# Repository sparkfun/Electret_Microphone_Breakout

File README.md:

Electret Microphone Breakout
============================

[*SparkFun Electret Microphone (BOB-09964)*](https://www.sparkfun.com/products/9964)

This small breakout board couples a small electret microphone 
with a 100x opamp to amplify the sounds of voice, door knocks, 
etc loud enough to be picked up by a microcontroller’s Analog to Digital converter. 

Repository Contents
-------------------
* **/Hardware** - All Eagle design files (.brd, .sch)

License Information
-------------------
The hardware is released under [Creative Commons ShareAlike 4.0 International](https://creativecommons.org/licenses/by-sa/4.0/).
The code is beerware; if you see me (or any other SparkFun employee) at the local, and you've found our code helpful, please buy us a round!

Distributed as-is; no warranty is given.

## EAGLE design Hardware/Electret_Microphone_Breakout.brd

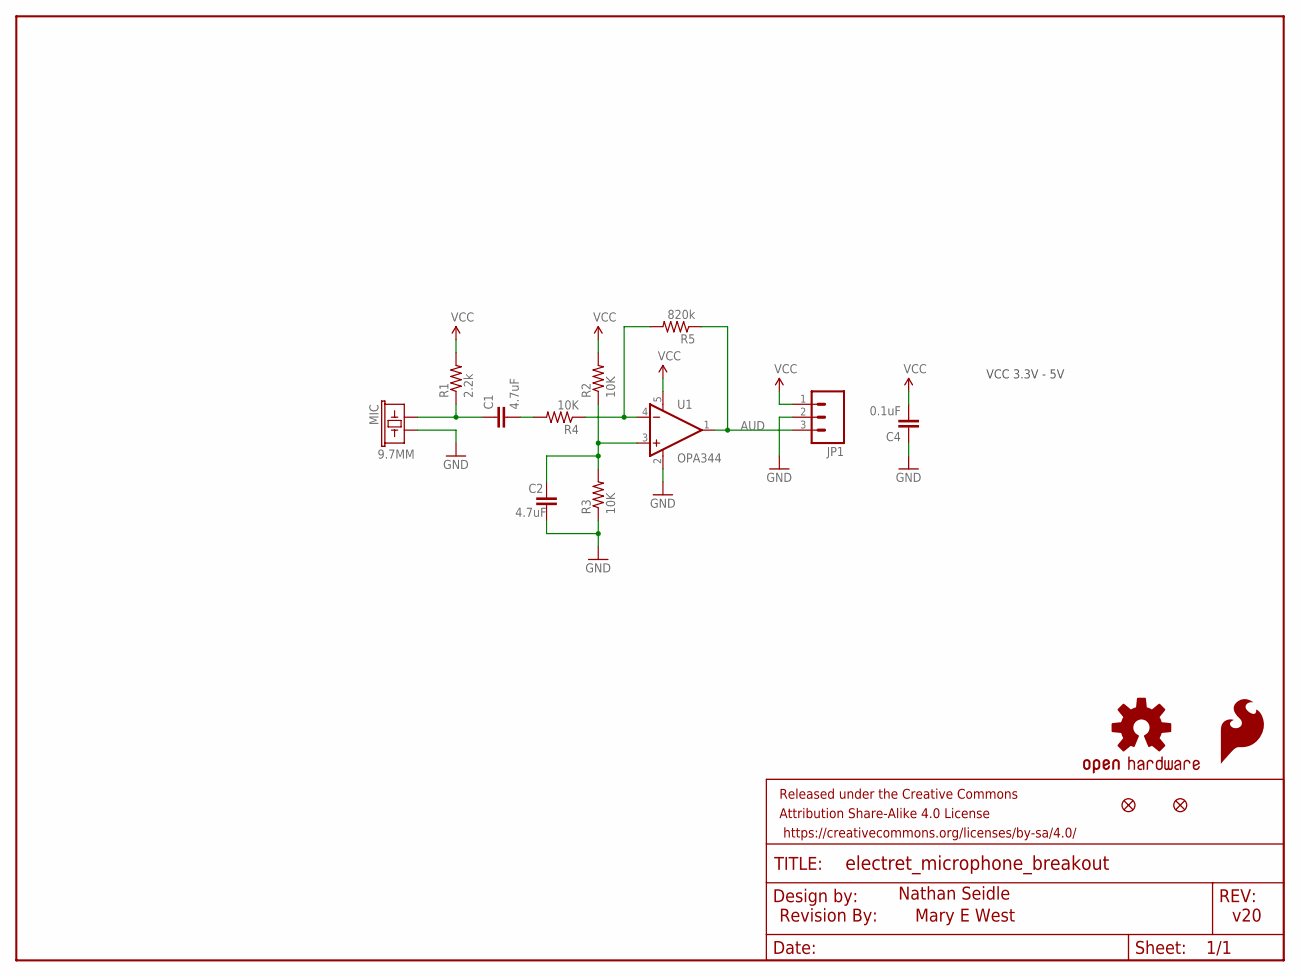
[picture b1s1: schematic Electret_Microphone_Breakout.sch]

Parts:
C1, C2: 4.7uF; 0603-CAP
C4: 0.1uF; 0603-CAP
FRAME1: FRAME-LETTER; CREATIVE_COMMONS
JP1: M03PTH; 1X03
JP2, JP3: FIDUCIALUFIDUCIAL; MICRO-FIDUCIAL
LOGO1: OSHW-LOGOMINI; OSHW-LOGO-MINI
MIC: 9.7MM; MIC-9.7MM
R1: 2.2k; 0603-RES
R2, R3, R4: 10K; 0603-RES
R5: 820k; 0603-RES
U1: OPA344; SOT23-5
U$1: SFE_LOGO_FLAME.1_INCH; SFE_LOGO_FLAME_.1
U$2: REVISION

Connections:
AUD: JP1.3, R5.1, U1.1 (OUT)
GND: C2.2, C4.1, JP1.2, MIC.2, R3.1, U1.2 (V-)
unnamed: C1.1, MIC.1, R1.1
unnamed: R4.1, R5.2, U1.4 (-IN)
unnamed: C1.2, R4.2
unnamed: C2.1, R2.1, R3.2, U1.3 (+IN)
VCC: C4.2, JP1.1, R1.2, R2.2, U1.5 (V+)

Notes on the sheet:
VCC 3.3V - 5V
v20
Mary E West
Nathan Seidle

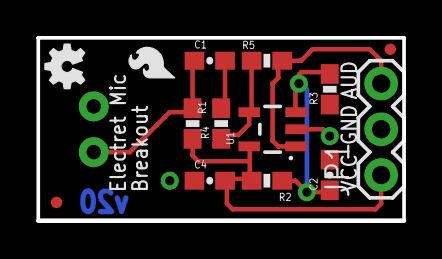
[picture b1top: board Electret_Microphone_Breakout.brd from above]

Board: 2 copper layers, 20.3 x 10.2 mm, 17 parts (1 on the bottom side), 7 nets.

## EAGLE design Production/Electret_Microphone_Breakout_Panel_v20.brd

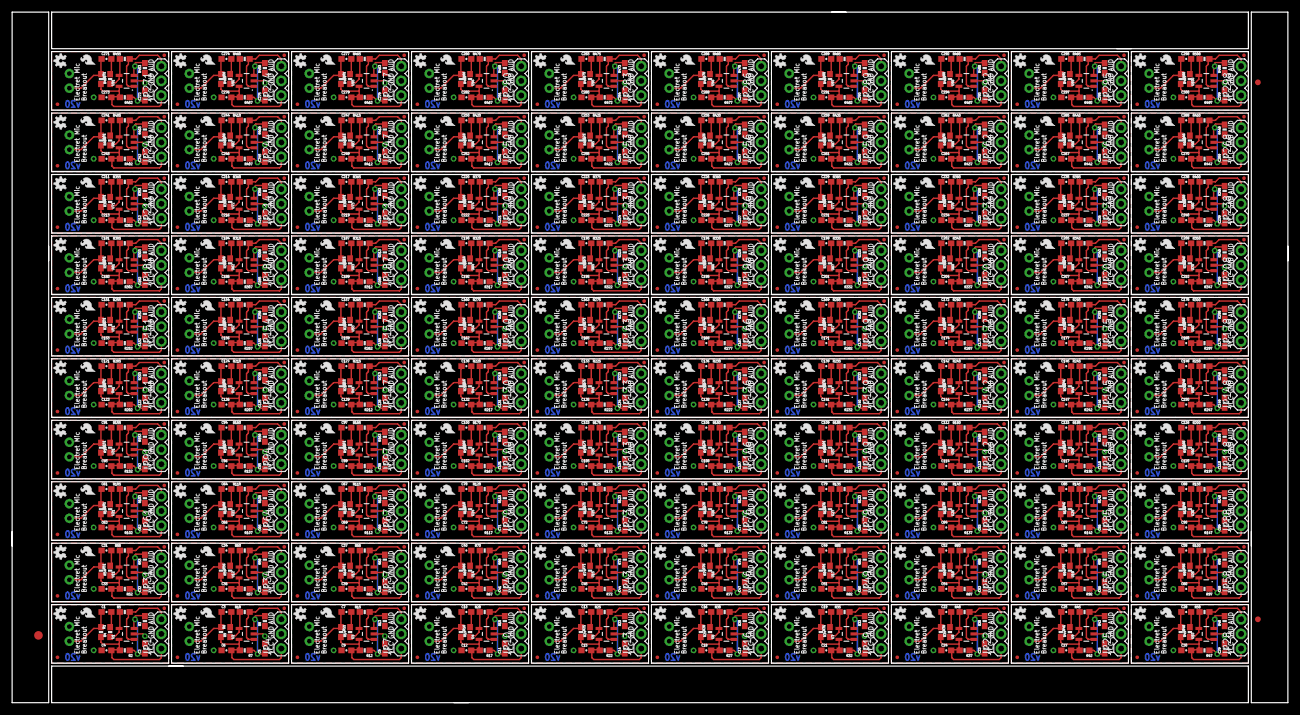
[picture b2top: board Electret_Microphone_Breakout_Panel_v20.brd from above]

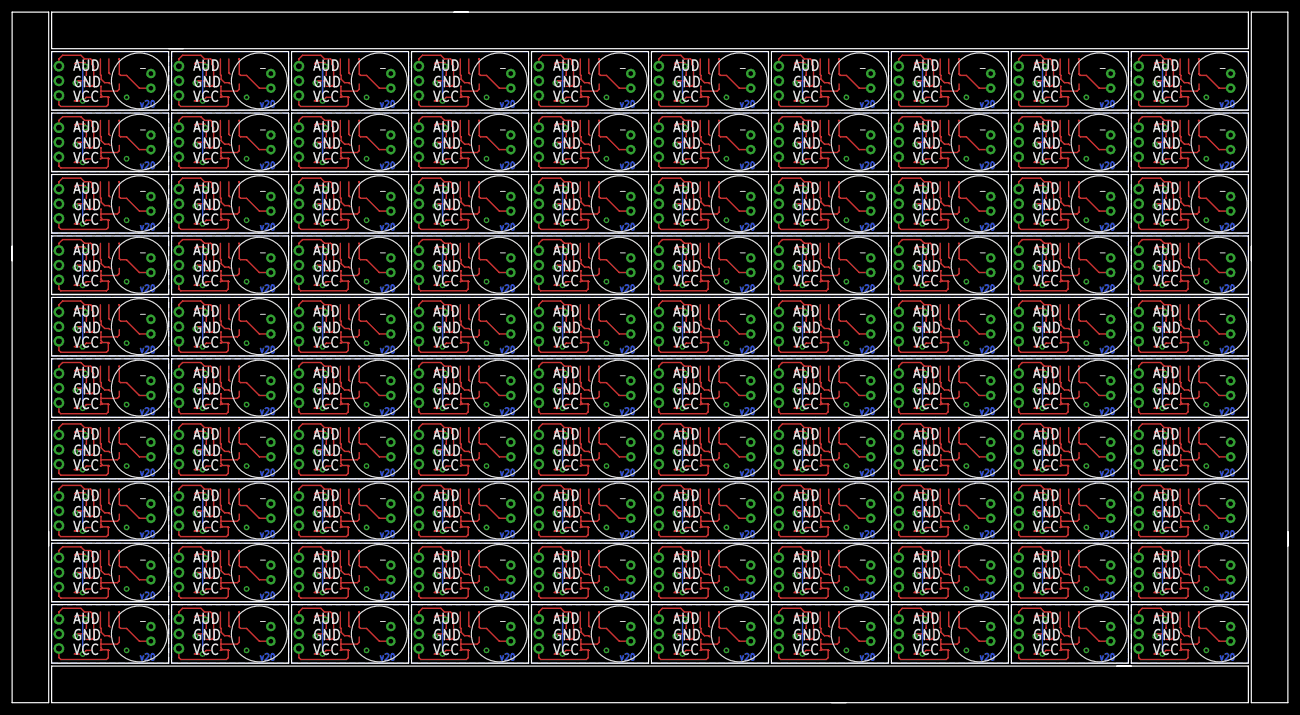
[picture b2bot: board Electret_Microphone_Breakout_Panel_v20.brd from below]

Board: 2 copper layers, 221.5 x 119.9 mm, 1503 parts (100 on the bottom side), 700 nets.

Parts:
C1, C2, C3, C5, C7, C8, C10, C11, C13, C14, C16, C17, C19, C20, C22, C23, C25, C26, C28, C29, C31, C32, C34, C35, C37, C38, C40, C41, C43, C44, C46, C47, C49, C50, C52, C53, C55, C56, C58, C59, C61, C62, C64, C65, C67, C68, C70, C71, C73, C74, C76, C77, C79, C80, C82, C83, C85, C86, C88, C89, C91, C92, C94, C95, C97, C98, C100, C101, C103, C104, C106, C107, C109, C110, C112, C113, C115, C116, C118, C119, C121, C122, C124, C125, C127, C128, C130, C131, C133, C134, C136, C137, C139, C140, C142, C143, C145, C146, C148, C149, C151, C152, C154, C155, C157, C158, C160, C161, C163, C164, C166, C167, C169, C170, C172, C173, C175, C176, C178, C179, C181, C182, C184, C185, C187, C188, C190, C191, C193, C194, C196, C197, C199, C200, C202, C203, C205, C206, C208, C209, C211, C212, C214, C215, C217, C218, C220, C221, C223, C224, C226, C227, C229, C230, C232, C233, C235, C236, C238, C239, C241, C242, C244, C245, C247, C248, C250, C251, C253, C254, C256, C257, C259, C260, C262, C263, C265, C266, C268, C269, C271, C272, C274, C275, C277, C278, C280, C281, C283, C284, C286, C287, C289, C290, C292, C293, C295, C296, C298, C299: 4.7uF; 0603-CAP
C4, C6, C9, C12, C15, C18, C21, C24, C27, C30, C33, C36, C39, C42, C45, C48, C51, C54, C57, C60, C63, C66, C69, C72, C75, C78, C81, C84, C87, C90, C93, C96, C99, C102, C105, C108, C111, C114, C117, C120, C123, C126, C129, C132, C135, C138, C141, C144, C147, C150, C153, C156, C159, C162, C165, C168, C171, C174, C177, C180, C183, C186, C189, C192, C195, C198, C201, C204, C207, C210, C213, C216, C219, C222, C225, C228, C231, C234, C237, C240, C243, C246, C249, C252, C255, C258, C261, C264, C267, C270, C273, C276, C279, C282, C285, C288, C291, C294, C297, C300: 0.1uF; 0603-CAP
E$1: FIDUCIAL-1.5X3
E$5, E$6: FIDUCIAL-1X2
JP1, JP4, JP7, JP10, JP13, JP16, JP19, JP22, JP25, JP28, JP31, JP34, JP37, JP40, JP43, JP46, JP49, JP52, JP55, JP58, JP61, JP64, JP67, JP70, JP73, JP76, JP79, JP82, JP85, JP88, JP91, JP94, JP97, JP100, JP103, JP106, JP109, JP112, JP115, JP118, JP121, JP124, JP127, JP130, JP133, JP136, JP139, JP142, JP145, JP148, JP151, JP154, JP157, JP160, JP163, JP166, JP169, JP172, JP175, JP178, JP181, JP184, JP187, JP190, JP193, JP196, JP199, JP202, JP205, JP208, JP211, JP214, JP217, JP220, JP223, JP226, JP229, JP232, JP235, JP238, JP241, JP244, JP247, JP250, JP253, JP256, JP259, JP262, JP265, JP268, JP271, JP274, JP277, JP280, JP283, JP286, JP289, JP292, JP295, JP298: 1X03
JP2, JP3, JP5, JP6, JP8, JP9, JP11, JP12, JP14, JP15, JP17, JP18, JP20, JP21, JP23, JP24, JP26, JP27, JP29, JP30, JP32, JP33, JP35, JP36, JP38, JP39, JP41, JP42, JP44, JP45, JP47, JP48, JP50, JP51, JP53, JP54, JP56, JP57, JP59, JP60, JP62, JP63, JP65, JP66, JP68, JP69, JP71, JP72, JP74, JP75, JP77, JP78, JP80, JP81, JP83, JP84, JP86, JP87, JP89, JP90, JP92, JP93, JP95, JP96, JP98, JP99, JP101, JP102, JP104, JP105, JP107, JP108, JP110, JP111, JP113, JP114, JP116, JP117, JP119, JP120, JP122, JP123, JP125, JP126, JP128, JP129, JP131, JP132, JP134, JP135, JP137, JP138, JP140, JP141, JP143, JP144, JP146, JP147, JP149, JP150, JP152, JP153, JP155, JP156, JP158, JP159, JP161, JP162, JP164, JP165, JP167, JP168, JP170, JP171, JP173, JP174, JP176, JP177, JP179, JP180, JP182, JP183, JP185, JP186, JP188, JP189, JP191, JP192, JP194, JP195, JP197, JP198, JP200, JP201, JP203, JP204, JP206, JP207, JP209, JP210, JP212, JP213, JP215, JP216, JP218, JP219, JP221, JP222, JP224, JP225, JP227, JP228, JP230, JP231, JP233, JP234, JP236, JP237, JP239, JP240, JP242, JP243, JP245, JP246, JP248, JP249, JP251, JP252, JP254, JP255, JP257, JP258, JP260, JP261, JP263, JP264, JP266, JP267, JP269, JP270, JP272, JP273, JP275, JP276, JP278, JP279, JP281, JP282, JP284, JP285, JP287, JP288, JP290, JP291, JP293, JP294, JP296, JP297, JP299, JP300: FIDUCIALUFIDUCIAL; MICRO-FIDUCIAL
LOGO1, LOGO2, LOGO3, LOGO4, LOGO5, LOGO6, LOGO7, LOGO8, LOGO9, LOGO10, LOGO11, LOGO12, LOGO13, LOGO14, LOGO15, LOGO16, LOGO17, LOGO18, LOGO19, LOGO20, LOGO21, LOGO22, LOGO23, LOGO24, LOGO25, LOGO26, LOGO27, LOGO28, LOGO29, LOGO30, LOGO31, LOGO32, LOGO33, LOGO34, LOGO35, LOGO36, LOGO37, LOGO38, LOGO39, LOGO40, LOGO41, LOGO42, LOGO43, LOGO44, LOGO45, LOGO46, LOGO47, LOGO48, LOGO49, LOGO50, LOGO51, LOGO52, LOGO53, LOGO54, LOGO55, LOGO56, LOGO57, LOGO58, LOGO59, LOGO60, LOGO61, LOGO62, LOGO63, LOGO64, LOGO65, LOGO66, LOGO67, LOGO68, LOGO69, LOGO70, LOGO71, LOGO72, LOGO73, LOGO74, LOGO75, LOGO76, LOGO77, LOGO78, LOGO79, LOGO80, LOGO81, LOGO82, LOGO83, LOGO84, LOGO85, LOGO86, LOGO87, LOGO88, LOGO89, LOGO90, LOGO91, LOGO92, LOGO93, LOGO94, LOGO95, LOGO96, LOGO97, LOGO98, LOGO99, LOGO100: OSHW-LOGOMINI; OSHW-LOGO-MINI
MIC, MIC1, MIC2, MIC3, MIC4, MIC5, MIC6, MIC7, MIC8, MIC9, MIC10, MIC11, MIC12, MIC13, MIC14, MIC15, MIC16, MIC17, MIC18, MIC19, MIC20, MIC21, MIC22, MIC23, MIC24, MIC25, MIC26, MIC27, MIC28, MIC29, MIC30, MIC31, MIC32, MIC33, MIC34, MIC35, MIC36, MIC37, MIC38, MIC39, MIC40, MIC41, MIC42, MIC43, MIC44, MIC45, MIC46, MIC47, MIC48, MIC49, MIC50, MIC51, MIC52, MIC53, MIC54, MIC55, MIC56, MIC57, MIC58, MIC59, MIC60, MIC61, MIC62, MIC63, MIC64, MIC65, MIC66, MIC67, MIC68, MIC69, MIC70, MIC71, MIC72, MIC73, MIC74, MIC75, MIC76, MIC77, MIC78, MIC79, MIC80, MIC81, MIC82, MIC83, MIC84, MIC85, MIC86, MIC87, MIC88, MIC89, MIC90, MIC91, MIC92, MIC93, MIC94, MIC95, MIC96, MIC97, MIC98, MIC99: 9.7MM; MIC-9.7MM
R1, R6, R11, R16, R21, R26, R31, R36, R41, R46, R51, R56, R61, R66, R71, R76, R81, R86, R91, R96, R101, R106, R111, R116, R121, R126, R131, R136, R141, R146, R151, R156, R161, R166, R171, R176, R181, R186, R191, R196, R201, R206, R211, R216, R221, R226, R231, R236, R241, R246, R251, R256, R261, R266, R271, R276, R281, R286, R291, R296, R301, R306, R311, R316, R321, R326, R331, R336, R341, R346, R351, R356, R361, R366, R371, R376, R381, R386, R391, R396, R401, R406, R411, R416, R421, R426, R431, R436, R441, R446, R451, R456, R461, R466, R471, R476, R481, R486, R491, R496: 2.2k; 0603-RES
R2, R3, R4, R7, R8, R9, R12, R13, R14, R17, R18, R19, R22, R23, R24, R27, R28, R29, R32, R33, R34, R37, R38, R39, R42, R43, R44, R47, R48, R49, R52, R53, R54, R57, R58, R59, R62, R63, R64, R67, R68, R69, R72, R73, R74, R77, R78, R79, R82, R83, R84, R87, R88, R89, R92, R93, R94, R97, R98, R99, R102, R103, R104, R107, R108, R109, R112, R113, R114, R117, R118, R119, R122, R123, R124, R127, R128, R129, R132, R133, R134, R137, R138, R139, R142, R143, R144, R147, R148, R149, R152, R153, R154, R157, R158, R159, R162, R163, R164, R167, R168, R169, R172, R173, R174, R177, R178, R179, R182, R183, R184, R187, R188, R189, R192, R193, R194, R197, R198, R199, R202, R203, R204, R207, R208, R209, R212, R213, R214, R217, R218, R219, R222, R223, R224, R227, R228, R229, R232, R233, R234, R237, R238, R239, R242, R243, R244, R247, R248, R249, R252, R253, R254, R257, R258, R259, R262, R263, R264, R267, R268, R269, R272, R273, R274, R277, R278, R279, R282, R283, R284, R287, R288, R289, R292, R293, R294, R297, R298, R299, R302, R303, R304, R307, R308, R309, R312, R313, R314, R317, R318, R319, R322, R323, R324, R327, R328, R329, R332, R333, R334, R337, R338, R339, R342, R343, R344, R347, R348, R349, R352, R353, R354, R357, R358, R359, R362, R363, R364, R367, R368, R369, R372, R373, R374, R377, R378, R379, R382, R383, R384, R387, R388, R389, R392, R393, R394, R397, R398, R399, R402, R403, R404, R407, R408, R409, R412, R413, R414, R417, R418, R419, R422, R423, R424, R427, R428, R429, R432, R433, R434, R437, R438, R439, R442, R443, R444, R447, R448, R449, R452, R453, R454, R457, R458, R459, R462, R463, R464, R467, R468, R469, R472, R473, R474, R477, R478, R479, R482, R483, R484, R487, R488, R489, R492, R493, R494, R497, R498, R499: 10K; 0603-RES
R5, R10, R15, R20, R25, R30, R35, R40, R45, R50, R55, R60, R65, R70, R75, R80, R85, R90, R95, R100, R105, R110, R115, R120, R125, R130, R135, R140, R145, R150, R155, R160, R165, R170, R175, R180, R185, R190, R195, R200, R205, R210, R215, R220, R225, R230, R235, R240, R245, R250, R255, R260, R265, R270, R275, R280, R285, R290, R295, R300, R305, R310, R315, R320, R325, R330, R335, R340, R345, R350, R355, R360, R365, R370, R375, R380, R385, R390, R395, R400, R405, R410, R415, R420, R425, R430, R435, R440, R445, R450, R455, R460, R465, R470, R475, R480, R485, R490, R495, R500: 820k; 0603-RES
U1, U2, U3, U4, U5, U6, U7, U8, U9, U10, U11, U12, U13, U14, U15, U16, U17, U18, U19, U20, U21, U22, U23, U24, U25, U26, U27, U28, U29, U30, U31, U32, U33, U34, U35, U36, U37, U38, U39, U40, U41, U42, U43, U44, U45, U46, U47, U48, U49, U50, U51, U52, U53, U54, U55, U56, U57, U58, U59, U60, U61, U62, U63, U64, U65, U66, U67, U68, U69, U70, U71, U72, U73, U74, U75, U76, U77, U78, U79, U80, U81, U82, U83, U84, U85, U86, U87, U88, U89, U90, U91, U92, U93, U94, U95, U96, U97, U98, U99, U100: OPA344; SOT23-5
U$1, U$2, U$3, U$4, U$5, U$6, U$7, U$8, U$9, U$10, U$11, U$12, U$13, U$14, U$15, U$16, U$17, U$18, U$19, U$20, U$21, U$22, U$23, U$24, U$25, U$26, U$27, U$28, U$29, U$30, U$31, U$32, U$33, U$34, U$35, U$36, U$37, U$38, U$39, U$40, U$41, U$42, U$43, U$44, U$45, U$46, U$47, U$48, U$49, U$50, U$51, U$52, U$53, U$54, U$55, U$56, U$57, U$58, U$59, U$60, U$61, U$62, U$63, U$64, U$65, U$66, U$67, U$68, U$69, U$70, U$71, U$72, U$73, U$74, U$75, U$76, U$77, U$78, U$79, U$80, U$81, U$82, U$83, U$84, U$85, U$86, U$87, U$88, U$89, U$90, U$91, U$92, U$93, U$94, U$95, U$96, U$97, U$98, U$99, U$100: SFE_LOGO_FLAME.1_INCH; SFE_LOGO_FLAME_.1

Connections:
AUD: JP1.3, R5.1, U1.1
AUD1: JP4.3, R10.1, U2.1
AUD2: JP7.3, R15.1, U3.1
AUD3: JP10.3, R20.1, U4.1
AUD4: JP13.3, R25.1, U5.1
AUD5: JP16.3, R30.1, U6.1
AUD6: JP19.3, R35.1, U7.1
AUD7: JP22.3, R40.1, U8.1
AUD8: JP25.3, R45.1, U9.1
AUD9: JP28.3, R50.1, U10.1
AUD10: JP31.3, R55.1, U11.1
AUD11: JP34.3, R60.1, U12.1
AUD12: JP37.3, R65.1, U13.1
AUD13: JP40.3, R70.1, U14.1
AUD14: JP43.3, R75.1, U15.1
AUD15: JP46.3, R80.1, U16.1
AUD16: JP49.3, R85.1, U17.1
AUD17: JP52.3, R90.1, U18.1
AUD18: JP55.3, R95.1, U19.1
AUD19: JP58.3, R100.1, U20.1
AUD20: JP61.3, R105.1, U21.1
AUD21: JP64.3, R110.1, U22.1
AUD22: JP67.3, R115.1, U23.1
AUD23: JP70.3, R120.1, U24.1
AUD24: JP73.3, R125.1, U25.1
AUD25: JP76.3, R130.1, U26.1
AUD26: JP79.3, R135.1, U27.1
AUD27: JP82.3, R140.1, U28.1
AUD28: JP85.3, R145.1, U29.1
AUD29: JP88.3, R150.1, U30.1
AUD30: JP91.3, R155.1, U31.1
AUD31: JP94.3, R160.1, U32.1
AUD32: JP97.3, R165.1, U33.1
AUD33: JP100.3, R170.1, U34.1
AUD34: JP103.3, R175.1, U35.1
AUD35: JP106.3, R180.1, U36.1
AUD36: JP109.3, R185.1, U37.1
AUD37: JP112.3, R190.1, U38.1
AUD38: JP115.3, R195.1, U39.1
AUD39: JP118.3, R200.1, U40.1
AUD40: JP121.3, R205.1, U41.1
AUD41: JP124.3, R210.1, U42.1
AUD42: JP127.3, R215.1, U43.1
AUD43: JP130.3, R220.1, U44.1
AUD44: JP133.3, R225.1, U45.1
AUD45: JP136.3, R230.1, U46.1
AUD46: JP139.3, R235.1, U47.1
AUD47: JP142.3, R240.1, U48.1
AUD48: JP145.3, R245.1, U49.1
AUD49: JP148.3, R250.1, U50.1
AUD50: JP151.3, R255.1, U51.1
AUD51: JP154.3, R260.1, U52.1
AUD52: JP157.3, R265.1, U53.1
AUD53: JP160.3, R270.1, U54.1
AUD54: JP163.3, R275.1, U55.1
AUD55: JP166.3, R280.1, U56.1
AUD56: JP169.3, R285.1, U57.1
AUD57: JP172.3, R290.1, U58.1
AUD58: JP175.3, R295.1, U59.1
AUD59: JP178.3, R300.1, U60.1
AUD60: JP181.3, R305.1, U61.1
AUD61: JP184.3, R310.1, U62.1
AUD62: JP187.3, R315.1, U63.1
AUD63: JP190.3, R320.1, U64.1
AUD64: JP193.3, R325.1, U65.1
AUD65: JP196.3, R330.1, U66.1
AUD66: JP199.3, R335.1, U67.1
AUD67: JP202.3, R340.1, U68.1
AUD68: JP205.3, R345.1, U69.1
AUD69: JP208.3, R350.1, U70.1
AUD70: JP211.3, R355.1, U71.1
AUD71: JP214.3, R360.1, U72.1
AUD72: JP217.3, R365.1, U73.1
AUD73: JP220.3, R370.1, U74.1
AUD74: JP223.3, R375.1, U75.1
AUD75: JP226.3, R380.1, U76.1
AUD76: JP229.3, R385.1, U77.1
AUD77: JP232.3, R390.1, U78.1
AUD78: JP235.3, R395.1, U79.1
AUD79: JP238.3, R400.1, U80.1
AUD80: JP241.3, R405.1, U81.1
AUD81: JP244.3, R410.1, U82.1
AUD82: JP247.3, R415.1, U83.1
AUD83: JP250.3, R420.1, U84.1
AUD84: JP253.3, R425.1, U85.1
AUD85: JP256.3, R430.1, U86.1
AUD86: JP259.3, R435.1, U87.1
AUD87: JP262.3, R440.1, U88.1
AUD88: JP265.3, R445.1, U89.1
AUD89: JP268.3, R450.1, U90.1
AUD90: JP271.3, R455.1, U91.1
AUD91: JP274.3, R460.1, U92.1
AUD92: JP277.3, R465.1, U93.1
AUD93: JP280.3, R470.1, U94.1
AUD94: JP283.3, R475.1, U95.1
AUD95: JP286.3, R480.1, U96.1
AUD96: JP289.3, R485.1, U97.1
AUD97: JP292.3, R490.1, U98.1
AUD98: JP295.3, R495.1, U99.1
AUD99: JP298.3, R500.1, U100.1
GND: C2.2, C4.1, JP1.2, MIC.2, R3.1, U1.2
GND1: C5.2, C6.1, JP4.2, MIC1.2, R8.1, U2.2
GND2: C8.2, C9.1, JP7.2, MIC2.2, R13.1, U3.2
GND3: C11.2, C12.1, JP10.2, MIC3.2, R18.1, U4.2
GND4: C14.2, C15.1, JP13.2, MIC4.2, R23.1, U5.2
GND5: C17.2, C18.1, JP16.2, MIC5.2, R28.1, U6.2
GND6: C20.2, C21.1, JP19.2, MIC6.2, R33.1, U7.2
GND7: C23.2, C24.1, JP22.2, MIC7.2, R38.1, U8.2
GND8: C26.2, C27.1, JP25.2, MIC8.2, R43.1, U9.2
GND9: C29.2, C30.1, JP28.2, MIC9.2, R48.1, U10.2
GND10: C32.2, C33.1, JP31.2, MIC10.2, R53.1, U11.2
GND11: C35.2, C36.1, JP34.2, MIC11.2, R58.1, U12.2
GND12: C38.2, C39.1, JP37.2, MIC12.2, R63.1, U13.2
GND13: C41.2, C42.1, JP40.2, MIC13.2, R68.1, U14.2
GND14: C44.2, C45.1, JP43.2, MIC14.2, R73.1, U15.2
GND15: C47.2, C48.1, JP46.2, MIC15.2, R78.1, U16.2
GND16: C50.2, C51.1, JP49.2, MIC16.2, R83.1, U17.2
GND17: C53.2, C54.1, JP52.2, MIC17.2, R88.1, U18.2
GND18: C56.2, C57.1, JP55.2, MIC18.2, R93.1, U19.2
GND19: C59.2, C60.1, JP58.2, MIC19.2, R98.1, U20.2
GND20: C62.2, C63.1, JP61.2, MIC20.2, R103.1, U21.2
GND21: C65.2, C66.1, JP64.2, MIC21.2, R108.1, U22.2
GND22: C68.2, C69.1, JP67.2, MIC22.2, R113.1, U23.2
GND23: C71.2, C72.1, JP70.2, MIC23.2, R118.1, U24.2
GND24: C74.2, C75.1, JP73.2, MIC24.2, R123.1, U25.2
GND25: C77.2, C78.1, JP76.2, MIC25.2, R128.1, U26.2
GND26: C80.2, C81.1, JP79.2, MIC26.2, R133.1, U27.2
GND27: C83.2, C84.1, JP82.2, MIC27.2, R138.1, U28.2
GND28: C86.2, C87.1, JP85.2, MIC28.2, R143.1, U29.2
GND29: C89.2, C90.1, JP88.2, MIC29.2, R148.1, U30.2
GND30: C92.2, C93.1, JP91.2, MIC30.2, R153.1, U31.2
GND31: C95.2, C96.1, JP94.2, MIC31.2, R158.1, U32.2
GND32: C98.2, C99.1, JP97.2, MIC32.2, R163.1, U33.2
GND33: C101.2, C102.1, JP100.2, MIC33.2, R168.1, U34.2
GND34: C104.2, C105.1, JP103.2, MIC34.2, R173.1, U35.2
GND35: C107.2, C108.1, JP106.2, MIC35.2, R178.1, U36.2
GND36: C110.2, C111.1, JP109.2, MIC36.2, R183.1, U37.2
GND37: C113.2, C114.1, JP112.2, MIC37.2, R188.1, U38.2
GND38: C116.2, C117.1, JP115.2, MIC38.2, R193.1, U39.2
GND39: C119.2, C120.1, JP118.2, MIC39.2, R198.1, U40.2
GND40: C122.2, C123.1, JP121.2, MIC40.2, R203.1, U41.2
GND41: C125.2, C126.1, JP124.2, MIC41.2, R208.1, U42.2
GND42: C128.2, C129.1, JP127.2, MIC42.2, R213.1, U43.2
GND43: C131.2, C132.1, JP130.2, MIC43.2, R218.1, U44.2
GND44: C134.2, C135.1, JP133.2, MIC44.2, R223.1, U45.2
GND45: C137.2, C138.1, JP136.2, MIC45.2, R228.1, U46.2
GND46: C140.2, C141.1, JP139.2, MIC46.2, R233.1, U47.2
GND47: C143.2, C144.1, JP142.2, MIC47.2, R238.1, U48.2
GND48: C146.2, C147.1, JP145.2, MIC48.2, R243.1, U49.2
GND49: C149.2, C150.1, JP148.2, MIC49.2, R248.1, U50.2
GND50: C152.2, C153.1, JP151.2, MIC50.2, R253.1, U51.2
GND51: C155.2, C156.1, JP154.2, MIC51.2, R258.1, U52.2
GND52: C158.2, C159.1, JP157.2, MIC52.2, R263.1, U53.2
GND53: C161.2, C162.1, JP160.2, MIC53.2, R268.1, U54.2
GND54: C164.2, C165.1, JP163.2, MIC54.2, R273.1, U55.2
GND55: C167.2, C168.1, JP166.2, MIC55.2, R278.1, U56.2
GND56: C170.2, C171.1, JP169.2, MIC56.2, R283.1, U57.2
GND57: C173.2, C174.1, JP172.2, MIC57.2, R288.1, U58.2
GND58: C176.2, C177.1, JP175.2, MIC58.2, R293.1, U59.2
GND59: C179.2, C180.1, JP178.2, MIC59.2, R298.1, U60.2
GND60: C182.2, C183.1, JP181.2, MIC60.2, R303.1, U61.2
GND61: C185.2, C186.1, JP184.2, MIC61.2, R308.1, U62.2
GND62: C188.2, C189.1, JP187.2, MIC62.2, R313.1, U63.2
GND63: C191.2, C192.1, JP190.2, MIC63.2, R318.1, U64.2
GND64: C194.2, C195.1, JP193.2, MIC64.2, R323.1, U65.2
GND65: C197.2, C198.1, JP196.2, MIC65.2, R328.1, U66.2
GND66: C200.2, C201.1, JP199.2, MIC66.2, R333.1, U67.2
GND67: C203.2, C204.1, JP202.2, MIC67.2, R338.1, U68.2
GND68: C206.2, C207.1, JP205.2, MIC68.2, R343.1, U69.2
GND69: C209.2, C210.1, JP208.2, MIC69.2, R348.1, U70.2
GND70: C212.2, C213.1, JP211.2, MIC70.2, R353.1, U71.2
GND71: C215.2, C216.1, JP214.2, MIC71.2, R358.1, U72.2
GND72: C218.2, C219.1, JP217.2, MIC72.2, R363.1, U73.2
GND73: C221.2, C222.1, JP220.2, MIC73.2, R368.1, U74.2
GND74: C224.2, C225.1, JP223.2, MIC74.2, R373.1, U75.2
GND75: C227.2, C228.1, JP226.2, MIC75.2, R378.1, U76.2
GND76: C230.2, C231.1, JP229.2, MIC76.2, R383.1, U77.2
GND77: C233.2, C234.1, JP232.2, MIC77.2, R388.1, U78.2
GND78: C236.2, C237.1, JP235.2, MIC78.2, R393.1, U79.2
GND79: C239.2, C240.1, JP238.2, MIC79.2, R398.1, U80.2
GND80: C242.2, C243.1, JP241.2, MIC80.2, R403.1, U81.2
GND81: C245.2, C246.1, JP244.2, MIC81.2, R408.1, U82.2
GND82: C248.2, C249.1, JP247.2, MIC82.2, R413.1, U83.2
GND83: C251.2, C252.1, JP250.2, MIC83.2, R418.1, U84.2
GND84: C254.2, C255.1, JP253.2, MIC84.2, R423.1, U85.2
GND85: C257.2, C258.1, JP256.2, MIC85.2, R428.1, U86.2
GND86: C260.2, C261.1, JP259.2, MIC86.2, R433.1, U87.2
GND87: C263.2, C264.1, JP262.2, MIC87.2, R438.1, U88.2
GND88: C266.2, C267.1, JP265.2, MIC88.2, R443.1, U89.2
GND89: C269.2, C270.1, JP268.2, MIC89.2, R448.1, U90.2
GND90: C272.2, C273.1, JP271.2, MIC90.2, R453.1, U91.2
GND91: C275.2, C276.1, JP274.2, MIC91.2, R458.1, U92.2
GND92: C278.2, C279.1, JP277.2, MIC92.2, R463.1, U93.2
GND93: C281.2, C282.1, JP280.2, MIC93.2, R468.1, U94.2
GND94: C284.2, C285.1, JP283.2, MIC94.2, R473.1, U95.2
GND95: C287.2, C288.1, JP286.2, MIC95.2, R478.1, U96.2
GND96: C290.2, C291.1, JP289.2, MIC96.2, R483.1, U97.2
GND97: C293.2, C294.1, JP292.2, MIC97.2, R488.1, U98.2
GND98: C296.2, C297.1, JP295.2, MIC98.2, R493.1, U99.2
GND99: C299.2, C300.1, JP298.2, MIC99.2, R498.1, U100.2
unnamed: C1.1, MIC.1, R1.1
unnamed: R4.1, R5.2, U1.4
unnamed: C3.1, MIC1.1, R6.1
unnamed: R9.1, R10.2, U2.4
unnamed: C1.2, R4.2
unnamed: C2.1, R2.1, R3.2, U1.3
unnamed: C3.2, R9.2
unnamed: C5.1, R7.1, R8.2, U2.3
unnamed: C7.1, MIC2.1, R11.1
unnamed: R14.1, R15.2, U3.4
unnamed: C7.2, R14.2
unnamed: C8.1, R12.1, R13.2, U3.3
unnamed: C10.1, MIC3.1, R16.1
unnamed: R19.1, R20.2, U4.4
unnamed: C10.2, R19.2
unnamed: C11.1, R17.1, R18.2, U4.3
unnamed: C13.1, MIC4.1, R21.1
unnamed: R24.1, R25.2, U5.4
unnamed: C13.2, R24.2
unnamed: C14.1, R22.1, R23.2, U5.3
unnamed: C16.1, MIC5.1, R26.1
unnamed: R29.1, R30.2, U6.4
unnamed: C16.2, R29.2
unnamed: C17.1, R27.1, R28.2, U6.3
unnamed: C19.1, MIC6.1, R31.1
unnamed: R34.1, R35.2, U7.4
unnamed: C19.2, R34.2
unnamed: C20.1, R32.1, R33.2, U7.3
unnamed: C22.1, MIC7.1, R36.1
unnamed: R39.1, R40.2, U8.4
unnamed: C22.2, R39.2
unnamed: C23.1, R37.1, R38.2, U8.3
unnamed: C25.1, MIC8.1, R41.1
unnamed: R44.1, R45.2, U9.4
unnamed: C25.2, R44.2
unnamed: C26.1, R42.1, R43.2, U9.3
unnamed: C28.1, MIC9.1, R46.1
unnamed: R49.1, R50.2, U10.4
unnamed: C28.2, R49.2
unnamed: C29.1, R47.1, R48.2, U10.3
unnamed: C31.1, MIC10.1, R51.1
unnamed: R54.1, R55.2, U11.4
unnamed: C31.2, R54.2
unnamed: C32.1, R52.1, R53.2, U11.3
unnamed: C34.1, MIC11.1, R56.1
unnamed: R59.1, R60.2, U12.4
unnamed: C34.2, R59.2
unnamed: C35.1, R57.1, R58.2, U12.3
unnamed: C37.1, MIC12.1, R61.1
unnamed: R64.1, R65.2, U13.4
unnamed: C37.2, R64.2
unnamed: C38.1, R62.1, R63.2, U13.3
unnamed: C40.1, MIC13.1, R66.1
unnamed: R69.1, R70.2, U14.4
unnamed: C40.2, R69.2
unnamed: C41.1, R67.1, R68.2, U14.3
unnamed: C43.1, MIC14.1, R71.1
unnamed: R74.1, R75.2, U15.4
unnamed: C43.2, R74.2
unnamed: C44.1, R72.1, R73.2, U15.3
unnamed: C46.1, MIC15.1, R76.1
unnamed: R79.1, R80.2, U16.4
unnamed: C46.2, R79.2
unnamed: C47.1, R77.1, R78.2, U16.3
unnamed: C49.1, MIC16.1, R81.1
unnamed: R84.1, R85.2, U17.4
unnamed: C49.2, R84.2
unnamed: C50.1, R82.1, R83.2, U17.3
unnamed: C52.1, MIC17.1, R86.1
unnamed: R89.1, R90.2, U18.4
unnamed: C52.2, R89.2
unnamed: C53.1, R87.1, R88.2, U18.3
unnamed: C55.1, MIC18.1, R91.1
unnamed: R94.1, R95.2, U19.4
unnamed: C55.2, R94.2
unnamed: C56.1, R92.1, R93.2, U19.3
unnamed: C58.1, MIC19.1, R96.1
unnamed: R99.1, R100.2, U20.4
unnamed: C58.2, R99.2
unnamed: C59.1, R97.1, R98.2, U20.3
unnamed: C61.1, MIC20.1, R101.1
unnamed: R104.1, R105.2, U21.4
unnamed: C61.2, R104.2
unnamed: C62.1, R102.1, R103.2, U21.3
unnamed: C64.1, MIC21.1, R106.1
unnamed: R109.1, R110.2, U22.4
unnamed: C64.2, R109.2
unnamed: C65.1, R107.1, R108.2, U22.3
unnamed: C67.1, MIC22.1, R111.1
unnamed: R114.1, R115.2, U23.4
unnamed: C67.2, R114.2
unnamed: C68.1, R112.1, R113.2, U23.3
unnamed: C70.1, MIC23.1, R116.1
unnamed: R119.1, R120.2, U24.4
unnamed: C70.2, R119.2
unnamed: C71.1, R117.1, R118.2, U24.3
unnamed: C73.1, MIC24.1, R121.1
unnamed: R124.1, R125.2, U25.4
unnamed: C73.2, R124.2
unnamed: C74.1, R122.1, R123.2, U25.3
unnamed: C76.1, MIC25.1, R126.1
unnamed: R129.1, R130.2, U26.4
unnamed: C76.2, R129.2
unnamed: C77.1, R127.1, R128.2, U26.3
unnamed: C79.1, MIC26.1, R131.1
unnamed: R134.1, R135.2, U27.4
unnamed: C79.2, R134.2
unnamed: C80.1, R132.1, R133.2, U27.3
unnamed: C82.1, MIC27.1, R136.1
unnamed: R139.1, R140.2, U28.4
unnamed: C82.2, R139.2
unnamed: C83.1, R137.1, R138.2, U28.3
unnamed: C85.1, MIC28.1, R141.1
unnamed: R144.1, R145.2, U29.4
unnamed: C85.2, R144.2
unnamed: C86.1, R142.1, R143.2, U29.3
unnamed: C88.1, MIC29.1, R146.1
unnamed: R149.1, R150.2, U30.4
unnamed: C88.2, R149.2
unnamed: C89.1, R147.1, R148.2, U30.3
unnamed: C91.1, MIC30.1, R151.1
unnamed: R154.1, R155.2, U31.4
unnamed: C91.2, R154.2
unnamed: C92.1, R152.1, R153.2, U31.3
unnamed: C94.1, MIC31.1, R156.1
unnamed: R159.1, R160.2, U32.4
unnamed: C94.2, R159.2
unnamed: C95.1, R157.1, R158.2, U32.3
unnamed: C97.1, MIC32.1, R161.1
unnamed: R164.1, R165.2, U33.4
unnamed: C97.2, R164.2
unnamed: C98.1, R162.1, R163.2, U33.3
unnamed: C100.1, MIC33.1, R166.1
unnamed: R169.1, R170.2, U34.4
unnamed: C100.2, R169.2
unnamed: C101.1, R167.1, R168.2, U34.3
unnamed: C103.1, MIC34.1, R171.1
unnamed: R174.1, R175.2, U35.4
unnamed: C103.2, R174.2
unnamed: C104.1, R172.1, R173.2, U35.3
unnamed: C106.1, MIC35.1, R176.1
unnamed: R179.1, R180.2, U36.4
unnamed: C106.2, R179.2
unnamed: C107.1, R177.1, R178.2, U36.3
unnamed: C109.1, MIC36.1, R181.1
unnamed: R184.1, R185.2, U37.4
unnamed: C109.2, R184.2
unnamed: C110.1, R182.1, R183.2, U37.3
unnamed: C112.1, MIC37.1, R186.1
unnamed: R189.1, R190.2, U38.4
unnamed: C112.2, R189.2
unnamed: C113.1, R187.1, R188.2, U38.3
unnamed: C115.1, MIC38.1, R191.1
unnamed: R194.1, R195.2, U39.4
unnamed: C115.2, R194.2
unnamed: C116.1, R192.1, R193.2, U39.3
unnamed: C118.1, MIC39.1, R196.1
unnamed: R199.1, R200.2, U40.4
unnamed: C118.2, R199.2
unnamed: C119.1, R197.1, R198.2, U40.3
unnamed: C121.1, MIC40.1, R201.1
unnamed: R204.1, R205.2, U41.4
unnamed: C121.2, R204.2
unnamed: C122.1, R202.1, R203.2, U41.3
unnamed: C124.1, MIC41.1, R206.1
unnamed: R209.1, R210.2, U42.4
unnamed: C124.2, R209.2
unnamed: C125.1, R207.1, R208.2, U42.3
unnamed: C127.1, MIC42.1, R211.1
unnamed: R214.1, R215.2, U43.4
unnamed: C127.2, R214.2
unnamed: C128.1, R212.1, R213.2, U43.3
unnamed: C130.1, MIC43.1, R216.1
unnamed: R219.1, R220.2, U44.4
unnamed: C130.2, R219.2
unnamed: C131.1, R217.1, R218.2, U44.3
unnamed: C133.1, MIC44.1, R221.1
unnamed: R224.1, R225.2, U45.4
unnamed: C133.2, R224.2
unnamed: C134.1, R222.1, R223.2, U45.3
unnamed: C136.1, MIC45.1, R226.1
unnamed: R229.1, R230.2, U46.4
unnamed: C136.2, R229.2
unnamed: C137.1, R227.1, R228.2, U46.3
unnamed: C139.1, MIC46.1, R231.1
unnamed: R234.1, R235.2, U47.4
unnamed: C139.2, R234.2
unnamed: C140.1, R232.1, R233.2, U47.3
unnamed: C142.1, MIC47.1, R236.1
unnamed: R239.1, R240.2, U48.4
unnamed: C142.2, R239.2
unnamed: C143.1, R237.1, R238.2, U48.3
unnamed: C145.1, MIC48.1, R241.1
unnamed: R244.1, R245.2, U49.4
unnamed: C145.2, R244.2
unnamed: C146.1, R242.1, R243.2, U49.3
unnamed: C148.1, MIC49.1, R246.1
unnamed: R249.1, R250.2, U50.4
unnamed: C148.2, R249.2
unnamed: C149.1, R247.1, R248.2, U50.3
unnamed: C151.1, MIC50.1, R251.1
unnamed: R254.1, R255.2, U51.4
unnamed: C151.2, R254.2
unnamed: C152.1, R252.1, R253.2, U51.3
unnamed: C154.1, MIC51.1, R256.1
unnamed: R259.1, R260.2, U52.4
unnamed: C154.2, R259.2
unnamed: C155.1, R257.1, R258.2, U52.3
unnamed: C157.1, MIC52.1, R261.1
unnamed: R264.1, R265.2, U53.4
unnamed: C157.2, R264.2
unnamed: C158.1, R262.1, R263.2, U53.3
unnamed: C160.1, MIC53.1, R266.1
unnamed: R269.1, R270.2, U54.4
unnamed: C160.2, R269.2
unnamed: C161.1, R267.1, R268.2, U54.3
unnamed: C163.1, MIC54.1, R271.1
unnamed: R274.1, R275.2, U55.4
unnamed: C163.2, R274.2
unnamed: C164.1, R272.1, R273.2, U55.3
unnamed: C166.1, MIC55.1, R276.1
unnamed: R279.1, R280.2, U56.4
unnamed: C166.2, R279.2
unnamed: C167.1, R277.1, R278.2, U56.3
unnamed: C169.1, MIC56.1, R281.1
unnamed: R284.1, R285.2, U57.4
unnamed: C169.2, R284.2
unnamed: C170.1, R282.1, R283.2, U57.3
unnamed: C172.1, MIC57.1, R286.1
unnamed: R289.1, R290.2, U58.4
unnamed: C172.2, R289.2
unnamed: C173.1, R287.1, R288.2, U58.3
unnamed: C175.1, MIC58.1, R291.1
unnamed: R294.1, R295.2, U59.4
unnamed: C175.2, R294.2
unnamed: C176.1, R292.1, R293.2, U59.3
unnamed: C178.1, MIC59.1, R296.1
unnamed: R299.1, R300.2, U60.4
unnamed: C178.2, R299.2
unnamed: C179.1, R297.1, R298.2, U60.3
unnamed: C181.1, MIC60.1, R301.1
unnamed: R304.1, R305.2, U61.4
unnamed: C181.2, R304.2
unnamed: C182.1, R302.1, R303.2, U61.3
unnamed: C184.1, MIC61.1, R306.1
unnamed: R309.1, R310.2, U62.4
unnamed: C184.2, R309.2
unnamed: C185.1, R307.1, R308.2, U62.3
unnamed: C187.1, MIC62.1, R311.1
unnamed: R314.1, R315.2, U63.4
unnamed: C187.2, R314.2
unnamed: C188.1, R312.1, R313.2, U63.3
unnamed: C190.1, MIC63.1, R316.1
unnamed: R319.1, R320.2, U64.4
unnamed: C190.2, R319.2
unnamed: C191.1, R317.1, R318.2, U64.3
unnamed: C193.1, MIC64.1, R321.1
unnamed: R324.1, R325.2, U65.4
unnamed: C193.2, R324.2
unnamed: C194.1, R322.1, R323.2, U65.3
unnamed: C196.1, MIC65.1, R326.1
unnamed: R329.1, R330.2, U66.4
unnamed: C196.2, R329.2
unnamed: C197.1, R327.1, R328.2, U66.3
unnamed: C199.1, MIC66.1, R331.1
unnamed: R334.1, R335.2, U67.4
unnamed: C199.2, R334.2
unnamed: C200.1, R332.1, R333.2, U67.3
unnamed: C202.1, MIC67.1, R336.1
unnamed: R339.1, R340.2, U68.4
unnamed: C202.2, R339.2
unnamed: C203.1, R337.1, R338.2, U68.3
unnamed: C205.1, MIC68.1, R341.1
unnamed: R344.1, R345.2, U69.4
unnamed: C205.2, R344.2
unnamed: C206.1, R342.1, R343.2, U69.3
unnamed: C208.1, MIC69.1, R346.1
unnamed: R349.1, R350.2, U70.4
unnamed: C208.2, R349.2
unnamed: C209.1, R347.1, R348.2, U70.3
unnamed: C211.1, MIC70.1, R351.1
unnamed: R354.1, R355.2, U71.4
unnamed: C211.2, R354.2
unnamed: C212.1, R352.1, R353.2, U71.3
unnamed: C214.1, MIC71.1, R356.1
unnamed: R359.1, R360.2, U72.4
unnamed: C214.2, R359.2
unnamed: C215.1, R357.1, R358.2, U72.3
unnamed: C217.1, MIC72.1, R361.1
unnamed: R364.1, R365.2, U73.4
unnamed: C217.2, R364.2
unnamed: C218.1, R362.1, R363.2, U73.3
unnamed: C220.1, MIC73.1, R366.1
unnamed: R369.1, R370.2, U74.4
unnamed: C220.2, R369.2
unnamed: C221.1, R367.1, R368.2, U74.3
unnamed: C223.1, MIC74.1, R371.1
unnamed: R374.1, R375.2, U75.4
unnamed: C223.2, R374.2
unnamed: C224.1, R372.1, R373.2, U75.3
unnamed: C226.1, MIC75.1, R376.1
unnamed: R379.1, R380.2, U76.4
unnamed: C226.2, R379.2
unnamed: C227.1, R377.1, R378.2, U76.3
unnamed: C229.1, MIC76.1, R381.1
unnamed: R384.1, R385.2, U77.4
unnamed: C229.2, R384.2
unnamed: C230.1, R382.1, R383.2, U77.3
unnamed: C232.1, MIC77.1, R386.1
unnamed: R389.1, R390.2, U78.4
unnamed: C232.2, R389.2
unnamed: C233.1, R387.1, R388.2, U78.3
unnamed: C235.1, MIC78.1, R391.1
unnamed: R394.1, R395.2, U79.4
unnamed: C235.2, R394.2
unnamed: C236.1, R392.1, R393.2, U79.3
unnamed: C238.1, MIC79.1, R396.1
unnamed: R399.1, R400.2, U80.4
unnamed: C238.2, R399.2
unnamed: C239.1, R397.1, R398.2, U80.3
unnamed: C241.1, MIC80.1, R401.1
unnamed: R404.1, R405.2, U81.4
unnamed: C241.2, R404.2
unnamed: C242.1, R402.1, R403.2, U81.3
unnamed: C244.1, MIC81.1, R406.1
unnamed: R409.1, R410.2, U82.4
unnamed: C244.2, R409.2
unnamed: C245.1, R407.1, R408.2, U82.3
unnamed: C247.1, MIC82.1, R411.1
unnamed: R414.1, R415.2, U83.4
unnamed: C247.2, R414.2
unnamed: C248.1, R412.1, R413.2, U83.3
unnamed: C250.1, MIC83.1, R416.1
unnamed: R419.1, R420.2, U84.4
unnamed: C250.2, R419.2
unnamed: C251.1, R417.1, R418.2, U84.3
unnamed: C253.1, MIC84.1, R421.1
unnamed: R424.1, R425.2, U85.4
unnamed: C253.2, R424.2
unnamed: C254.1, R422.1, R423.2, U85.3
unnamed: C256.1, MIC85.1, R426.1
unnamed: R429.1, R430.2, U86.4
unnamed: C256.2, R429.2
unnamed: C257.1, R427.1, R428.2, U86.3
unnamed: C259.1, MIC86.1, R431.1
unnamed: R434.1, R435.2, U87.4
unnamed: C259.2, R434.2
unnamed: C260.1, R432.1, R433.2, U87.3
unnamed: C262.1, MIC87.1, R436.1
unnamed: R439.1, R440.2, U88.4
unnamed: C262.2, R439.2
unnamed: C263.1, R437.1, R438.2, U88.3
unnamed: C265.1, MIC88.1, R441.1
unnamed: R444.1, R445.2, U89.4
unnamed: C265.2, R444.2
unnamed: C266.1, R442.1, R443.2, U89.3
unnamed: C268.1, MIC89.1, R446.1
unnamed: R449.1, R450.2, U90.4
unnamed: C268.2, R449.2
unnamed: C269.1, R447.1, R448.2, U90.3
unnamed: C271.1, MIC90.1, R451.1
unnamed: R454.1, R455.2, U91.4
unnamed: C271.2, R454.2
unnamed: C272.1, R452.1, R453.2, U91.3
unnamed: C274.1, MIC91.1, R456.1
unnamed: R459.1, R460.2, U92.4
unnamed: C274.2, R459.2
unnamed: C275.1, R457.1, R458.2, U92.3
unnamed: C277.1, MIC92.1, R461.1
unnamed: R464.1, R465.2, U93.4
unnamed: C277.2, R464.2
unnamed: C278.1, R462.1, R463.2, U93.3
unnamed: C280.1, MIC93.1, R466.1
unnamed: R469.1, R470.2, U94.4
unnamed: C280.2, R469.2
unnamed: C281.1, R467.1, R468.2, U94.3
unnamed: C283.1, MIC94.1, R471.1
unnamed: R474.1, R475.2, U95.4
unnamed: C283.2, R474.2
unnamed: C284.1, R472.1, R473.2, U95.3
unnamed: C286.1, MIC95.1, R476.1
unnamed: R479.1, R480.2, U96.4
unnamed: C286.2, R479.2
unnamed: C287.1, R477.1, R478.2, U96.3
unnamed: C289.1, MIC96.1, R481.1
unnamed: R484.1, R485.2, U97.4
unnamed: C289.2, R484.2
unnamed: C290.1, R482.1, R483.2, U97.3
unnamed: C292.1, MIC97.1, R486.1
unnamed: R489.1, R490.2, U98.4
unnamed: C292.2, R489.2
unnamed: C293.1, R487.1, R488.2, U98.3
unnamed: C295.1, MIC98.1, R491.1
unnamed: R494.1, R495.2, U99.4
unnamed: C295.2, R494.2
unnamed: C296.1, R492.1, R493.2, U99.3
unnamed: C298.1, MIC99.1, R496.1
unnamed: R499.1, R500.2, U100.4
unnamed: C298.2, R499.2
unnamed: C299.1, R497.1, R498.2, U100.3
VCC: C4.2, JP1.1, R1.2, R2.2, U1.5
VCC1: C6.2, JP4.1, R6.2, R7.2, U2.5
VCC2: C9.2, JP7.1, R11.2, R12.2, U3.5
VCC3: C12.2, JP10.1, R16.2, R17.2, U4.5
VCC4: C15.2, JP13.1, R21.2, R22.2, U5.5
VCC5: C18.2, JP16.1, R26.2, R27.2, U6.5
VCC6: C21.2, JP19.1, R31.2, R32.2, U7.5
VCC7: C24.2, JP22.1, R36.2, R37.2, U8.5
VCC8: C27.2, JP25.1, R41.2, R42.2, U9.5
VCC9: C30.2, JP28.1, R46.2, R47.2, U10.5
VCC10: C33.2, JP31.1, R51.2, R52.2, U11.5
VCC11: C36.2, JP34.1, R56.2, R57.2, U12.5
VCC12: C39.2, JP37.1, R61.2, R62.2, U13.5
VCC13: C42.2, JP40.1, R66.2, R67.2, U14.5
VCC14: C45.2, JP43.1, R71.2, R72.2, U15.5
VCC15: C48.2, JP46.1, R76.2, R77.2, U16.5
VCC16: C51.2, JP49.1, R81.2, R82.2, U17.5
VCC17: C54.2, JP52.1, R86.2, R87.2, U18.5
VCC18: C57.2, JP55.1, R91.2, R92.2, U19.5
VCC19: C60.2, JP58.1, R96.2, R97.2, U20.5
VCC20: C63.2, JP61.1, R101.2, R102.2, U21.5
VCC21: C66.2, JP64.1, R106.2, R107.2, U22.5
VCC22: C69.2, JP67.1, R111.2, R112.2, U23.5
VCC23: C72.2, JP70.1, R116.2, R117.2, U24.5
VCC24: C75.2, JP73.1, R121.2, R122.2, U25.5
VCC25: C78.2, JP76.1, R126.2, R127.2, U26.5
VCC26: C81.2, JP79.1, R131.2, R132.2, U27.5
VCC27: C84.2, JP82.1, R136.2, R137.2, U28.5
VCC28: C87.2, JP85.1, R141.2, R142.2, U29.5
VCC29: C90.2, JP88.1, R146.2, R147.2, U30.5
VCC30: C93.2, JP91.1, R151.2, R152.2, U31.5
VCC31: C96.2, JP94.1, R156.2, R157.2, U32.5
VCC32: C99.2, JP97.1, R161.2, R162.2, U33.5
VCC33: C102.2, JP100.1, R166.2, R167.2, U34.5
VCC34: C105.2, JP103.1, R171.2, R172.2, U35.5
VCC35: C108.2, JP106.1, R176.2, R177.2, U36.5
VCC36: C111.2, JP109.1, R181.2, R182.2, U37.5
VCC37: C114.2, JP112.1, R186.2, R187.2, U38.5
VCC38: C117.2, JP115.1, R191.2, R192.2, U39.5
VCC39: C120.2, JP118.1, R196.2, R197.2, U40.5
VCC40: C123.2, JP121.1, R201.2, R202.2, U41.5
VCC41: C126.2, JP124.1, R206.2, R207.2, U42.5
VCC42: C129.2, JP127.1, R211.2, R212.2, U43.5
VCC43: C132.2, JP130.1, R216.2, R217.2, U44.5
VCC44: C135.2, JP133.1, R221.2, R222.2, U45.5
VCC45: C138.2, JP136.1, R226.2, R227.2, U46.5
VCC46: C141.2, JP139.1, R231.2, R232.2, U47.5
VCC47: C144.2, JP142.1, R236.2, R237.2, U48.5
VCC48: C147.2, JP145.1, R241.2, R242.2, U49.5
VCC49: C150.2, JP148.1, R246.2, R247.2, U50.5
VCC50: C153.2, JP151.1, R251.2, R252.2, U51.5
VCC51: C156.2, JP154.1, R256.2, R257.2, U52.5
VCC52: C159.2, JP157.1, R261.2, R262.2, U53.5
VCC53: C162.2, JP160.1, R266.2, R267.2, U54.5
VCC54: C165.2, JP163.1, R271.2, R272.2, U55.5
VCC55: C168.2, JP166.1, R276.2, R277.2, U56.5
VCC56: C171.2, JP169.1, R281.2, R282.2, U57.5
VCC57: C174.2, JP172.1, R286.2, R287.2, U58.5
VCC58: C177.2, JP175.1, R291.2, R292.2, U59.5
VCC59: C180.2, JP178.1, R296.2, R297.2, U60.5
VCC60: C183.2, JP181.1, R301.2, R302.2, U61.5
VCC61: C186.2, JP184.1, R306.2, R307.2, U62.5
VCC62: C189.2, JP187.1, R311.2, R312.2, U63.5
VCC63: C192.2, JP190.1, R316.2, R317.2, U64.5
VCC64: C195.2, JP193.1, R321.2, R322.2, U65.5
VCC65: C198.2, JP196.1, R326.2, R327.2, U66.5
VCC66: C201.2, JP199.1, R331.2, R332.2, U67.5
VCC67: C204.2, JP202.1, R336.2, R337.2, U68.5
VCC68: C207.2, JP205.1, R341.2, R342.2, U69.5
VCC69: C210.2, JP208.1, R346.2, R347.2, U70.5
VCC70: C213.2, JP211.1, R351.2, R352.2, U71.5
VCC71: C216.2, JP214.1, R356.2, R357.2, U72.5
VCC72: C219.2, JP217.1, R361.2, R362.2, U73.5
VCC73: C222.2, JP220.1, R366.2, R367.2, U74.5
VCC74: C225.2, JP223.1, R371.2, R372.2, U75.5
VCC75: C228.2, JP226.1, R376.2, R377.2, U76.5
VCC76: C231.2, JP229.1, R381.2, R382.2, U77.5
VCC77: C234.2, JP232.1, R386.2, R387.2, U78.5
VCC78: C237.2, JP235.1, R391.2, R392.2, U79.5
VCC79: C240.2, JP238.1, R396.2, R397.2, U80.5
VCC80: C243.2, JP241.1, R401.2, R402.2, U81.5
VCC81: C246.2, JP244.1, R406.2, R407.2, U82.5
VCC82: C249.2, JP247.1, R411.2, R412.2, U83.5
VCC83: C252.2, JP250.1, R416.2, R417.2, U84.5
VCC84: C255.2, JP253.1, R421.2, R422.2, U85.5
VCC85: C258.2, JP256.1, R426.2, R427.2, U86.5
VCC86: C261.2, JP259.1, R431.2, R432.2, U87.5
VCC87: C264.2, JP262.1, R436.2, R437.2, U88.5
VCC88: C267.2, JP265.1, R441.2, R442.2, U89.5
VCC89: C270.2, JP268.1, R446.2, R447.2, U90.5
VCC90: C273.2, JP271.1, R451.2, R452.2, U91.5
VCC91: C276.2, JP274.1, R456.2, R457.2, U92.5
VCC92: C279.2, JP277.1, R461.2, R462.2, U93.5
VCC93: C282.2, JP280.1, R466.2, R467.2, U94.5
VCC94: C285.2, JP283.1, R471.2, R472.2, U95.5
VCC95: C288.2, JP286.1, R476.2, R477.2, U96.5
VCC96: C291.2, JP289.1, R481.2, R482.2, U97.5
VCC97: C294.2, JP292.1, R486.2, R487.2, U98.5
VCC98: C297.2, JP295.1, R491.2, R492.2, U99.5
VCC99: C300.2, JP298.1, R496.2, R497.2, U100.5

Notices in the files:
parts and their libraries:
SparkFun-Aesthetics: Licensing: Creative Commons ShareAlike 4.0 International - https://creativecommons.org/licenses/by-sa/4.0
SparkFun-Aesthetics: Released under the Creative Commons Attribution Share-Alike 4.0 License
SparkFun-Aesthetics: Released under the Creative Commons
